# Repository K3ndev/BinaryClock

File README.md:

# Binary Clock

## Clock for programers

### Features

- Built in tiredness detector (if you cant read it you need to sleep)
- You can start conversations with it
- You can feel superior if you can read the time from it
- Displays the time in binary

### How can you make it?

1. Order the pcb (a stencil is recommended)
2. Order the parts from the [BOM](#bill-of-materials)
3. Print the holder
4. Solder in everything
5. Screw it up with 2 M2 screws
6. Plug the usb-c in
7. Set the time with the buttons
8. You got your Binary clock

### Bill of Materials

The full BOM with footprints is in [`BOM.csv`](BOM.csv). LCSC prices were checked on 2026-11-01 and converted at 1 USD = 327.9 HUF; PCB, holder and shipping costs are manual estimates.

| Reference | Qty | Value | LCSC | Unit price (USD) | Line total (USD) | Line total (HUF) |
|:--|--:|:--|:--|--:|--:|--:|
| C1, C4–C17, C19 | 16 | 100nF | [C1591](https://www.lcsc.com/product-detail/C1591.html) | $0.0075 | $0.12 | 39.35 Ft |
| C2, C3 | 2 | 22 pF | [C326840](https://www.lcsc.com/product-detail/C326840.html) | $0.0149 | $0.0298 | 9.77 Ft |
| C18 | 1 | 100uF 35V | [C72478](https://www.lcsc.com/product-detail/C72478.html) | $0.0338 | $0.0338 | 11.08 Ft |
| D1–D24 | 24 | Green LED | [C375482](https://www.lcsc.com/product-detail/C375482.html) | $0.0261 | $0.6264 | 205.40 Ft |
| J1 | 1 | USB-C receptacle 6P | [C18357552](https://www.lcsc.com/product-detail/C18357552.html) | $0.0467 | $0.0467 | 15.31 Ft |
| R1 | 1 | 330k | [C2907027](https://www.lcsc.com/product-detail/C2907027.html) | $0.002 | $0.002 | 0.66 Ft |
| R2 | 1 | 10M | [C2930145](https://www.lcsc.com/product-detail/C2930145.html) | $0.0024 | $0.0024 | 0.79 Ft |
| R3, R5, R7, R9 | 4 | 100k | [C14675](https://www.lcsc.com/product-detail/C14675.html) | $0.0022 | $0.0088 | 2.89 Ft |
| R4, R6, R8, R10 | 4 | 10k | [C98220](https://www.lcsc.com/product-detail/C98220.html) | $0.0027 | $0.0108 | 3.54 Ft |
| R11, R12 | 2 | 5.1k | [C2907044](https://www.lcsc.com/product-detail/C2907044.html) | $0.0018 | $0.0036 | 1.18 Ft |
| RN1–RN6 | 6 | 330Ω | [C12018](https://www.lcsc.com/product-detail/C12018.html) | $0.0214 | $0.1284 | 42.10 Ft |
| SW1–SW4 | 4 | SW_Push 6x6x5.5mm | [C42416244](https://www.lcsc.com/product-detail/C42416244.html) | $0.0203 | $0.0812 | 26.63 Ft |
| U1 | 1 | 4013 | [C13527](https://www.lcsc.com/product-detail/C13527.html) | $0.2526 | $0.2526 | 82.83 Ft |
| U2 | 1 | 4060 | [C134017](https://www.lcsc.com/product-detail/C134017.html) | $0.4094 | $0.4094 | 134.24 Ft |
| U3, U10 | 2 | 4081 | [C40551](https://www.lcsc.com/product-detail/C40551.html) | $0.3278 | $0.6556 | 214.97 Ft |
| U4–U6, U8–U9, U11 | 6 | 4510 | [C2862976](https://www.lcsc.com/product-detail/C2862976.html) | $0.8473 | $5.0838 | 1,666.98 Ft |
| U7 | 1 | 4071 | [C97039](https://www.lcsc.com/product-detail/C97039.html) | $0.4982 | $0.4982 | 163.36 Ft |
| Y1 | 1 | 32.768 kHz | [C3034396](https://www.lcsc.com/product-detail/C3034396.html) | $0.0972 | $0.0972 | 31.87 Ft |
| PCB | 1 | 2 layer | - | $11.22 | $11.22 | 3,679.00 Ft |
| 3D printing filament used| 1 | 35 g | - | $1.00 | $1.00 | 330.00 Ft |
| screw | 2 | M2 - 6mm | - | $0.16 | $0.33 | 100 Ft |
| Shipping | 1 | - | - | $10.00 | $10.00 | 3,000.00 Ft |
| **Total (one clock)** | | | | | **$30.31** | **9,661.95 Ft** |
| **Total (LCSC minimum order)** | | | | | **$37.22** | **11,926.29 Ft** |

The minimum-order total is higher because LCSC sells some parts in larger minimum quantities (for example 100 pcs of the 0603 resistors) even though only a few are needed per board.

I 3d printed the washer for it because its better than a metal one for the pcb.

### How it works

The crystals Hz is divided down to 1 Hz and it gives the circuit the clock.
T
here are some binary counter ic. The first one gets the clock straight from the crystal.

The others are getting from an AND gate with 4 input what is watching that the output of the pervious ic is don't flow over the limit. When all of the inputs are high it send a signal to de next ic's clock pin and the watched ic reset pin.
The counter pins are go straight to the leds trough a resistor.

There are 4 buttons. Those are for setting the time. Those buttons signal goes trough a low pass filter and a pulldown resistor to prevent multiple inputs in a same time. and the signals end at the ic's clock pin.

It's just a stand for the pcb

### License

This project is licensed under the MIT License - see the LICENSE file for details.

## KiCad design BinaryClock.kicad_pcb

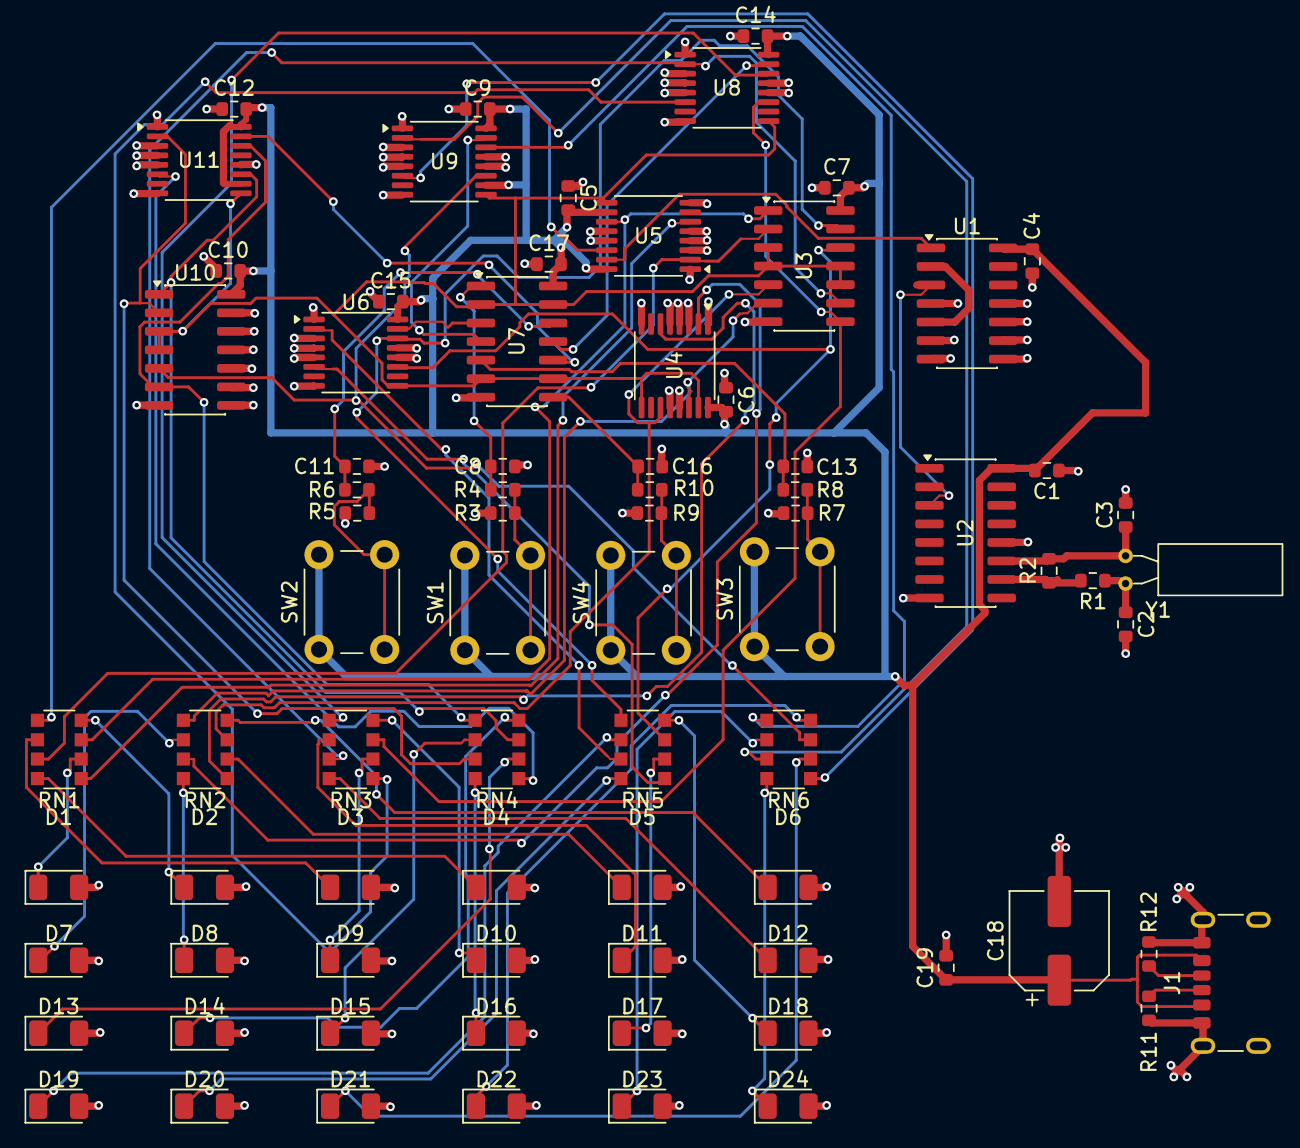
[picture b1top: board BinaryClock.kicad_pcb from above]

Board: 2 copper layers, 78 parts (0 on the bottom side), 71 nets.

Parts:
C1, C4, C5, C6, C7, C8, C9, C10, C11, C12, C13, C14, C15, C16, C17, C19: 100nF; R_0603_1608Metric
C2, C3: 22 pF; R_0603_1608Metric
C18: 10uF; CP_Elec_6.3x7.7
D1, D2, D3, D4, D5, D6, D7, D8, D9, D10, D11, D12, D13, D14, D15, D16, D17, D18, D19, D20, D21, D22, D23, D24: LED; LED_1206_3216Metric
J1: USB_C_Receptacle_PowerOnly_6P; USB_C_Receptacle_GCT_USB4125-xx-x-0190_6P_TopMnt_Horizontal
R1: 330k; R_0603_1608Metric
R2: 10M; R_0603_1608Metric
R3, R5, R7, R9: 100k; R_0603_1608Metric
R4, R6, R8, R10: 10k; R_0603_1608Metric
R11, R12: 5.1k; R_0603_1608Metric
RN1, RN2, RN3, RN4, RN5, RN6: R_Pack04_SIP; R_Array_Convex_4x1206
SW1, SW2, SW3, SW4: SW_Push_Dual; SW_PUSH_6mm_H5mm
U1: 4013; SOIC-14_3.9x8.7mm_P1.27mm
U2: 4060; SOIC-16_3.9x9.9mm_P1.27mm
U3, U10: 4081; SOIC-14_3.9x8.7mm_P1.27mm
U4, U5, U6, U8, U9, U11: 4510; TSSOP-16_4.4x5mm_P0.65mm
U7: 4071; SOIC-14_3.9x8.7mm_P1.27mm
Y1: 32.768 kHz; Crystal_C38-LF_D3.0mm_L8.0mm_Horizontal

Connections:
+5V: C1.2, C4.2, C5.2, C6.2, C7.2, C9.2, C10.2, C12.2, C14.2, C15.2, C17.2, C18.1, C19.1, J1.A9 (VBUS), J1.B9 (VBUS), SW1.1, SW2.1, SW3.1, SW4.1, U1.14 (VDD), U2.16 (VDD), U3.14 (VDD), U4.10 (U/D), U4.16 (VDD), U5.10 (U/D), U5.16 (VDD), U6.10 (U/D), U6.16 (VDD), U7.14 (VDD), U8.10 (U/D), U8.16 (VDD), U9.10 (U/D), U9.16 (VDD), U10.14 (VDD), U11.10 (U/D), U11.16 (VDD)
/Clk/CLK: U1.1 (Q), U5.15 (CLK)
/Counters/hour/24h_RST: U3.3, U3.4, U3.10, U3.11, U4.9 (RST), U4.15 (CLK), U5.9 (RST), U6.9 (RST), U7.2, U7.6, U7.9, U7.13, U8.9 (RST), U9.9 (RST), U10.3, U10.4, U11.9 (RST)
/Counters/hour/hour-o_1: RN4.1 (R1.1), U11.6 (Q1)
/Counters/hour/hour-o_2: RN4.3 (R2.1), U10.1, U11.11 (Q2)
/Counters/hour/hour-o_3: RN4.5 (R3.1), U10.6, U11.14 (Q3)
/Counters/hour/hour-o_4: RN4.7 (R4.1), U10.2, U11.2 (Q4)
/Counters/hour/hour-t_1: RN6.1 (R1.1), U9.6 (Q1)
/Counters/hour/hour-t_2: RN6.3 (R2.1), U9.11 (Q2), U10.5
/Counters/hour/hour-t_3: RN6.5 (R3.1), U9.14 (Q3)
/Counters/hour/hour-t_4: RN6.7 (R4.1), U9.2 (Q4)
/Counters/min/min-o_1: RN3.1 (R1.1), U8.6 (Q1)
/Counters/min/min-o_2: RN3.3 (R2.1), U3.8, U8.11 (Q2)
/Counters/min/min-o_3: RN3.5 (R3.1), U8.14 (Q3)
/Counters/min/min-o_4: RN3.7 (R4.1), U3.9, U8.2 (Q4)
/Counters/min/min-t_1: RN5.1 (R1.1), U6.6 (Q1)
/Counters/min/min-t_2: RN5.3 (R2.1), U3.12, U6.11 (Q2)
/Counters/min/min-t_3: RN5.5 (R3.1), U3.13, U6.14 (Q3)
/Counters/min/min-t_4: RN5.7 (R4.1), U6.2 (Q4)
/Counters/sec/sec-o_1: RN1.1 (R1.1), U5.6 (Q1)
/Counters/sec/sec-o_2: RN1.3 (R2.1), U3.1, U5.11 (Q2)
/Counters/sec/sec-o_3: RN1.5 (R3.1), U5.14 (Q3)
/Counters/sec/sec-o_4: RN1.7 (R4.1), U3.2, U5.2 (Q4)
/Counters/sec/sec-t_1: RN2.1 (R1.1), U4.6 (Q1)
/Counters/sec/sec-t_2: RN2.3 (R2.1), U3.5, U4.11 (Q2)
/Counters/sec/sec-t_3: RN2.5 (R3.1), U3.6, U4.14 (Q3)
/Counters/sec/sec-t_4: RN2.7 (R4.1), U4.2 (Q4)
GND: C1.1, C2.2, C3.2, C4.1, C5.1, C6.1, C7.1, C8.1, C9.1, C10.1, C11.1, C12.1, C13.1, C14.1, C15.1, C16.1, C17.1, C18.2, C19.2, D1.2 (A), D2.2 (A), D3.2 (A), D4.2 (A), D5.2 (A), D6.2 (A), D7.2 (A), D8.2 (A), D9.2 (A), D10.2 (A), D11.2 (A), D12.2 (A), D13.2 (A), D14.2 (A), D15.2 (A), D16.2 (A), D17.2 (A), D18.2 (A), D19.2 (A), D20.2 (A), D21.2 (A), D22.2 (A), D23.2 (A), D24.2 (A), J1.A12 (GND), J1.B12 (GND), J1.SH (SHIELD), R3.2, R5.2, R7.2, R9.2, R11.1, R12.2, U1.4 (R), U1.6 (S), U1.7 (VSS), U1.8 (S), U1.9 (D), U1.10 (R), U1.11 (C), U2.8 (VSS), U2.12 (CLR), U3.7 (VSS), U4.1 (PE), U4.3 (A4), U4.4 (A1), U4.5 (CI), U4.8 (VSS), U4.12 (A2), U4.13 (A3), U5.1 (PE), U5.3 (A4), U5.4 (A1), U5.5 (CI), U5.8 (VSS), U5.12 (A2), U5.13 (A3), U6.1 (PE), U6.3 (A4), U6.4 (A1), U6.5 (CI), U6.8 (VSS), U6.12 (A2), U6.13 (A3), U7.7 (VSS), U8.1 (PE), U8.3 (A4), U8.4 (A1), U8.5 (CI), U8.8 (VSS), U8.12 (A2), U8.13 (A3), U9.1 (PE), U9.3 (A4), U9.4 (A1), U9.5 (CI), U9.8 (VSS), U9.12 (A2), U9.13 (A3), U10.7 (VSS), U10.8, U10.9, U10.10, U10.11, U10.12, U10.13, U11.1 (PE), U11.3 (A4), U11.4 (A1), U11.5 (CI), U11.8 (VSS), U11.12 (A2), U11.13 (A3)
unnamed: C2.1, R1.1, Y1.1
unnamed: C8.2, R4.2, U7.1
unnamed: C11.2, R6.2, U7.12
unnamed: C13.2, R8.2, U7.5
unnamed: C16.2, R10.2, U7.8
unnamed: D1.1 (K), RN1.2 (R1.2)
unnamed: D2.1 (K), RN1.4 (R2.2)
unnamed: D3.1 (K), RN1.6 (R3.2)
unnamed: D4.1 (K), RN1.8 (R4.2)
unnamed: D5.1 (K), RN2.2 (R1.2)
unnamed: D6.1 (K), RN2.4 (R2.2)
unnamed: D7.1 (K), RN2.6 (R3.2)
unnamed: D8.1 (K), RN2.8 (R4.2)
unnamed: D9.1 (K), RN3.2 (R1.2)
unnamed: D10.1 (K), RN3.4 (R2.2)
unnamed: D11.1 (K), RN3.6 (R3.2)
unnamed: D12.1 (K), RN3.8 (R4.2)
unnamed: D13.1 (K), RN4.2 (R1.2)
unnamed: D14.1 (K), RN4.4 (R2.2)
unnamed: D15.1 (K), RN4.6 (R3.2)
unnamed: D16.1 (K), RN4.8 (R4.2)
unnamed: D17.1 (K), RN5.2 (R1.2)
unnamed: D18.1 (K), RN5.4 (R2.2)
unnamed: D19.1 (K), RN5.6 (R3.2)
unnamed: D20.1 (K), RN5.8 (R4.2)
unnamed: D21.1 (K), RN6.2 (R1.2)
unnamed: D22.1 (K), RN6.4 (R2.2)
unnamed: D23.1 (K), RN6.6 (R3.2)
unnamed: D24.1 (K), RN6.8 (R4.2)
unnamed: J1.A5 (CC1), R11.2
unnamed: J1.B5 (CC2), R12.1
unnamed: R3.1, R4.1, SW1.2
unnamed: R5.1, R6.1, SW2.2
unnamed: R7.1, R8.1, SW3.2
unnamed: R9.1, R10.1, SW4.2
unnamed: U1.3 (C), U2.3 (Q14)
unnamed: U1.2 (~Q), U1.5 (D)
unnamed: C3.1, R2.2, U2.11 (~Φ1), Y1.2
unnamed: R1.2, R2.1, U2.10 (Φ0)
unnamed: U6.15 (CLK), U7.3
unnamed: U7.11, U8.15 (CLK)
unnamed: U7.4, U9.15 (CLK)
unnamed: U7.10, U11.15 (CLK)

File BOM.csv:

"Reference","Qty","Value","DNP","Footprint","LCSC Part"
"C1,C4,C5,C6,C7,C8,C9,C10,C11,C12,C13,C14,C15,C16,C17,C19","16","100nF","","Resistor_SMD:R_0603_1608Metric","C1591"
"C2,C3","2","22 pF","","Resistor_SMD:R_0603_1608Metric","C326840"
"C18","1","10uF","","Capacitor_SMD:CP_Elec_6.3x7.7","C72478"
"D1,D2,D3,D4,D5,D6,D7,D8,D9,D10,D11,D12,D13,D14,D15,D16,D17,D18,D19,D20,D21,D22,D23,D24","24","LED","","LED_SMD:LED_1206_3216Metric","C375482"
"J1","1","USB_C_Receptacle_PowerOnly_6P","","Connector_USB:USB_C_Receptacle_GCT_USB4125-xx-x-0190_6P_TopMnt_Horizontal","C18357552"
"R1","1","330k","","Resistor_SMD:R_0603_1608Metric","C2907027"
"R2","1","10M","","Resistor_SMD:R_0603_1608Metric","C2930145"
"R3,R5,R7,R9","4","100k","","Resistor_SMD:R_0603_1608Metric","C14675"
"R4,R6,R8,R10","4","10k","","Resistor_SMD:R_0603_1608Metric","C98220"
"R11,R12","2","5.1k","","Resistor_SMD:R_0603_1608Metric","C2907044"
"RN1,RN2,RN3,RN4,RN5,RN6","6","R_Pack04_SIP","","Resistor_SMD:R_Array_Convex_4x1206","C12018"
"SW1,SW2,SW3,SW4","4","SW_Push_Dual","","Button_Switch_THT:SW_PUSH_6mm_H5mm","C42416244"
"U1","1","4013","","Package_SO:SOIC-14_3.9x8.7mm_P1.27mm","C13527"
"U2","1","4060","","Package_SO:SOIC-16_3.9x9.9mm_P1.27mm","C134017"
"U3,U10","2","4081","","Package_SO:SOIC-14_3.9x8.7mm_P1.27mm","C40551"
"U4,U5,U6,U8,U9,U11","6","4510","","Package_SO:TSSOP-16_4.4x5mm_P0.65mm","C2862976"
"U7","1","4071","","Package_SO:SOIC-14_3.9x8.7mm_P1.27mm","C97039"
"Y1","1","32.768 kHz","","Crystal:Crystal_C38-LF_D3.0mm_L8.0mm_Horizontal","C3034396"
